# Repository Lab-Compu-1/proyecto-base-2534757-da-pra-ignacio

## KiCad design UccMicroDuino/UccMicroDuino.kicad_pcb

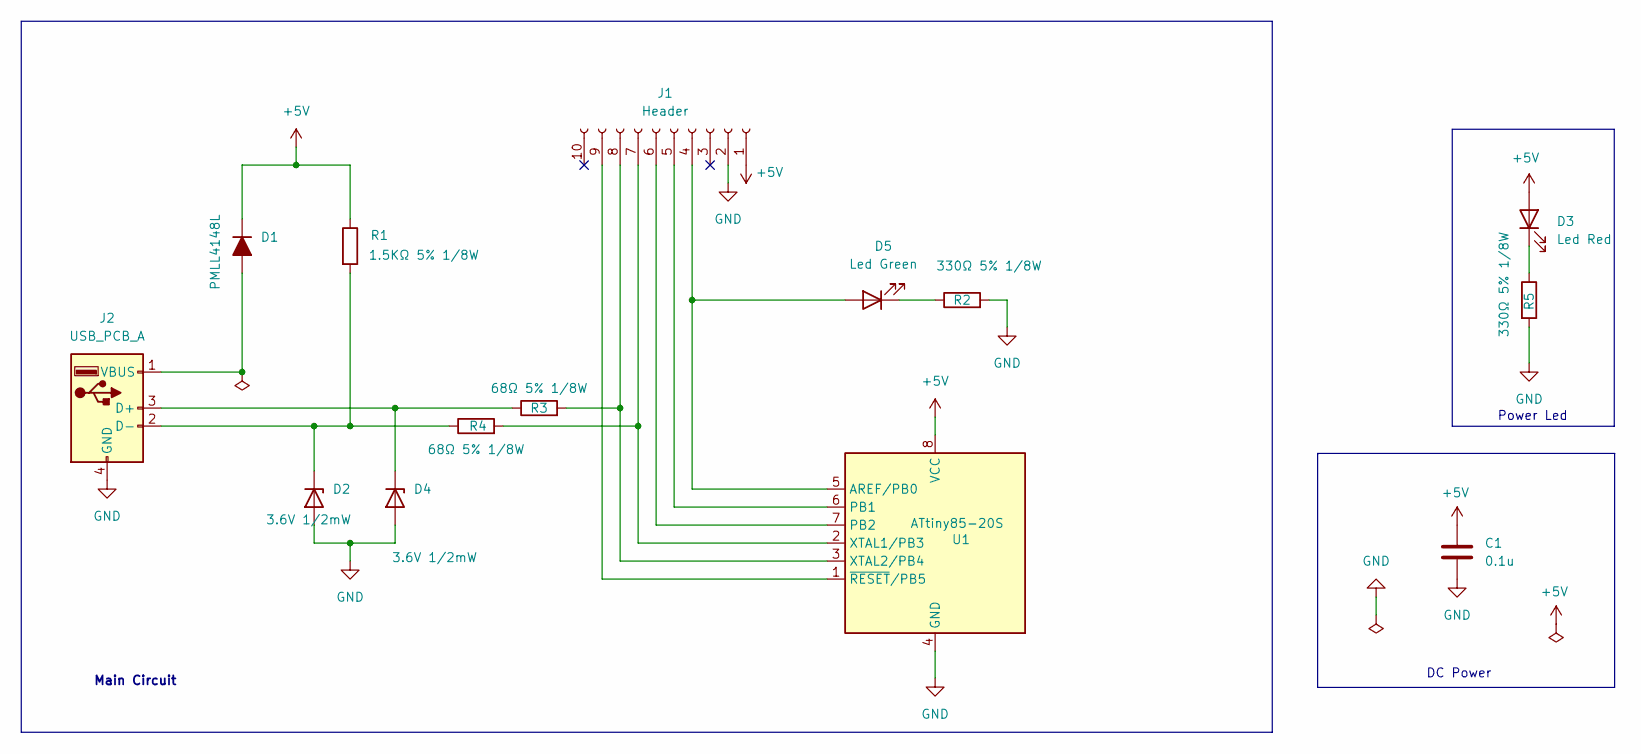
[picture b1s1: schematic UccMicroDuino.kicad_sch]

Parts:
C1: 0.1u; C_0805_2012Metric_Pad1.18x1.45mm_HandSolder
D1: PMLL4148L; D_MiniMELF
D2, D4: 3.6V 1/2mW; D_SOD-123
D3: Led Red; ledSMD
D5: Led Green; ledSMD
J1: Header; PinHeader_1x10_P2.54mm_Vertical
J2: USB_PCB_A; USB_A_UCC
R1: 1.5KΩ 5% 1/8W; R_0805_2012Metric_Pad1.20x1.40mm_HandSolder
R2, R5: 330Ω 5% 1/8W; R_0805_2012Metric_Pad1.20x1.40mm_HandSolder
R3, R4: 68Ω 5% 1/8W; R_0805_2012Metric_Pad1.20x1.40mm_HandSolder
U1: ATtiny85-20S; SOIC-8_5.3x5.3mm_P1.27mm

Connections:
+5V: C1.1, D1.1 (K), D3.2 (A), J1.1, R1.1, U1.8 (VCC)
GND: C1.2, D2.2 (A), D4.2 (A), J1.2, J2.4 (GND), R2.2, R5.2, U1.4 (GND)
unnamed: D1.2 (A), J2.1 (VBUS)
unnamed: D2.1 (K), J2.2 (D-), R1.2, R4.1
unnamed: D3.1 (K), R5.1
unnamed: D4.1 (K), J2.3 (D+), R3.1
unnamed: D5.2 (A), J1.4, U1.5 (AREF/PB0)
unnamed: D5.1 (K), R2.1
unnamed: J1.5, U1.6 (PB1)
unnamed: J1.6, U1.7 (PB2)
unnamed: J1.7, R4.2, U1.2 (XTAL1/PB3)
unnamed: J1.8, R3.2, U1.3 (XTAL2/PB4)
unnamed: J1.9, U1.1 (~RESET/PB5)

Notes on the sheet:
Power Led
Main Circuit
DC Power

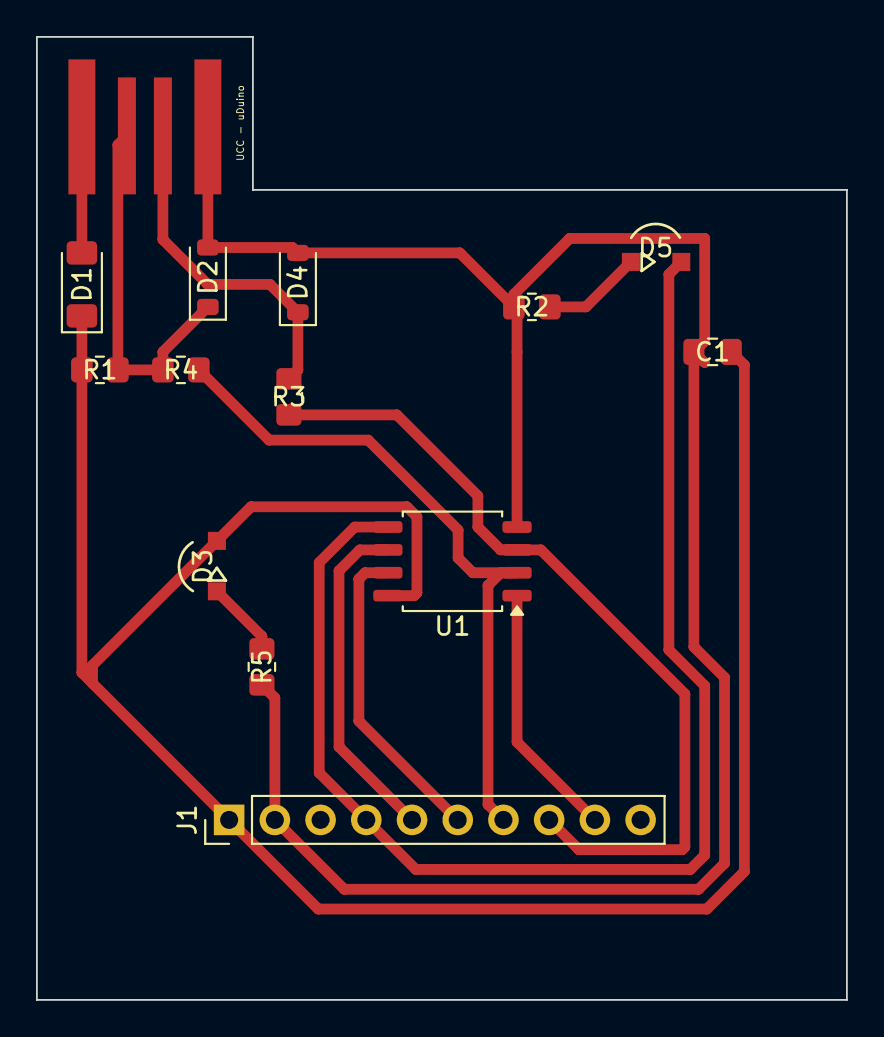
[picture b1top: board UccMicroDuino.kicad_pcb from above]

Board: 2 copper layers, 45.0 x 53.5 mm, 14 parts (0 on the bottom side), 13 nets.

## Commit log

2026-03-30 GitHub Classroom Feedback
2026-03-30 Setting up GitHub Classroom Feedback
2026-05-31 Agrego proyecto UccMicroDuino
2026-05-31 Agrego texto al PCB
2026-05-31 Agrego programa Blink
2026-06-01 Remuevo Blink del repositorio del proyecto
